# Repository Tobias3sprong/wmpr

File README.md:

# Weller WMPR
Weller WMPR Solder controller

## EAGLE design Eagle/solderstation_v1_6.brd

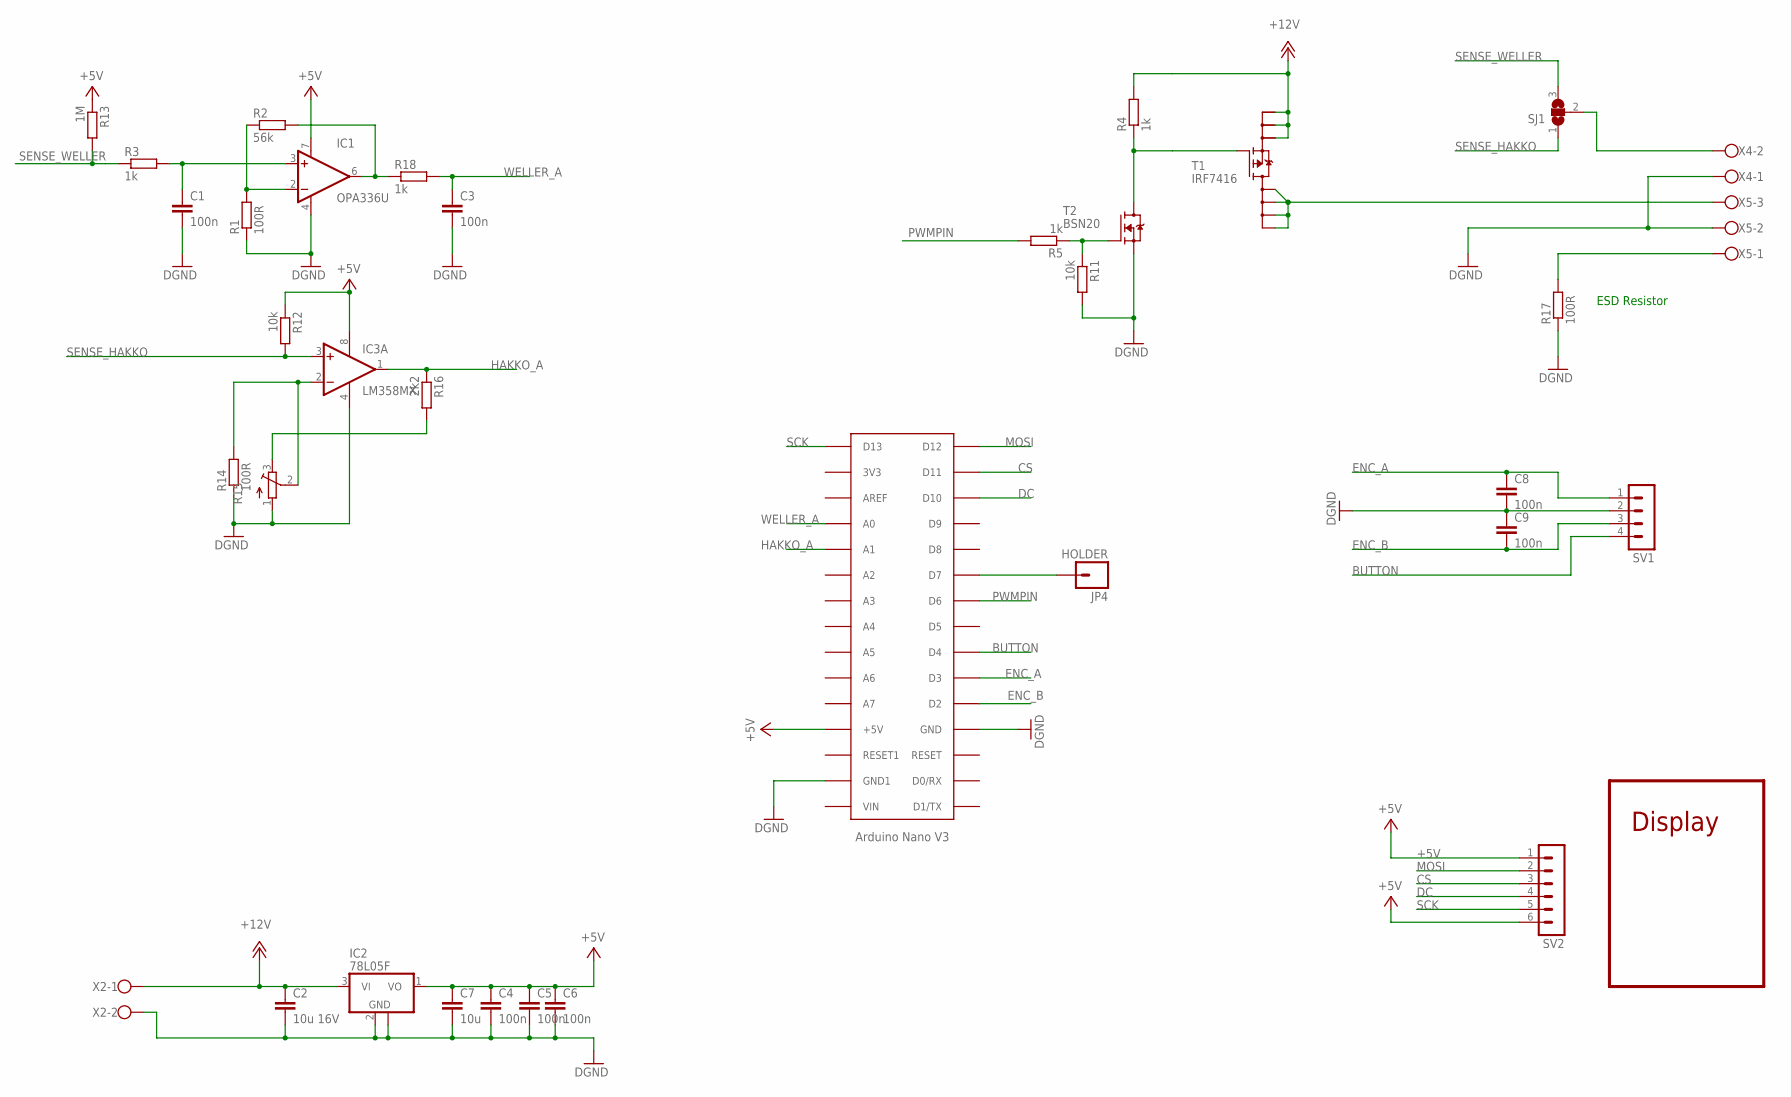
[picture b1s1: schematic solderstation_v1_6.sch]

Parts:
C1, C3, C4, C5, C6, C8, C9: 100n; C1206
C2: 10u 16V; C1210K
C7: 10u; C1210K
IC1: OPA336U; SO08
IC2: 78L05F; SOT89
IC3: LM358MX; SO08
JP4: HOLDER; 1X01
R1, R14, R17: 100R; R0603
R2: 56k; R0603
R3, R4, R5, R18: 1k; R0603
R11, R12: 10k; R0603
R13: 1M; R0603
R15: TRIM_EU-SM-42/43X; SM-42/43X
R16: 2k2; R0603
SJ1: SJ2W; SJ_2
SV1: MA04-1
SV2: MA06-1
T1: IRF7416; SO8
T2: BSN20; SOT23
U$6: ARDUINONANO; PDIP-32
X2, X4: W237-102
X5: W237-103

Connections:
+5V: C4.1, C5.1, C6.1, C7.1, IC1.7 (V+), IC2.1 (VO), IC3.8 (V+), R12.1, R13.1, SV2.1, SV2.6, U$6.+5V
+12V: C2.1, IC2.3 (VI), R4.2, T1.1 (S0), T1.2 (S1), T1.3 (S2), X2.1
BUTTON: SV1.4, U$6.D4
CS: SV2.3, U$6.D11
DC: SV2.4, U$6.D10
DGND: C1.2, C2.2, C3.2, C4.2, C5.2, C6.2, C7.2, C8.2, C9.1, IC1.4 (V-), IC2.2 (GND), IC2.2@1 (GND), IC3.4 (V-), R1.1, R11.2, R14.1, R15.1 (A), R17.1, SV1.2, T2.2 (S), U$6.GND, U$6.GND1, X2.2, X4.1, X5.2
ENC_A: C8.1, SV1.1, U$6.D3
ENC_B: C9.2, SV1.3, U$6.D2
HAKKO_A: IC3.1 (OUT), R16.1, U$6.A6 (A1)
HEATER: T1.5 (D0), T1.6 (D1), T1.7 (D2), T1.8 (D3), X5.3
MOSI: SV2.2, U$6.D12
unnamed: IC1.2 (-IN), R1.2, R2.1
unnamed: IC1.6 (OUT), R2.2, R18.1
unnamed: R5.1, R11.1, T2.1 (G)
unnamed: C1.1, IC1.3 (+IN), R3.2
unnamed: R4.1, T1.4 (G), T2.3 (D)
unnamed: SJ1.2, X4.2
unnamed: R15.3 (E), R16.2
unnamed: IC3.2 (-IN), R14.2, R15.2 (S)
unnamed: JP4.1, U$6.D7
unnamed: R17.2, X5.1
PWMPIN: R5.2, U$6.D6
SCK: SV2.5, U$6.D13
SENSE_HAKKO: IC3.3 (+IN), R12.2, SJ1.1
SENSE_WELLER: R3.1, R13.2, SJ1.3
WELLER_A: C3.1, R18.2, U$6.A7 (A0)

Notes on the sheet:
Display
ESD Resistor

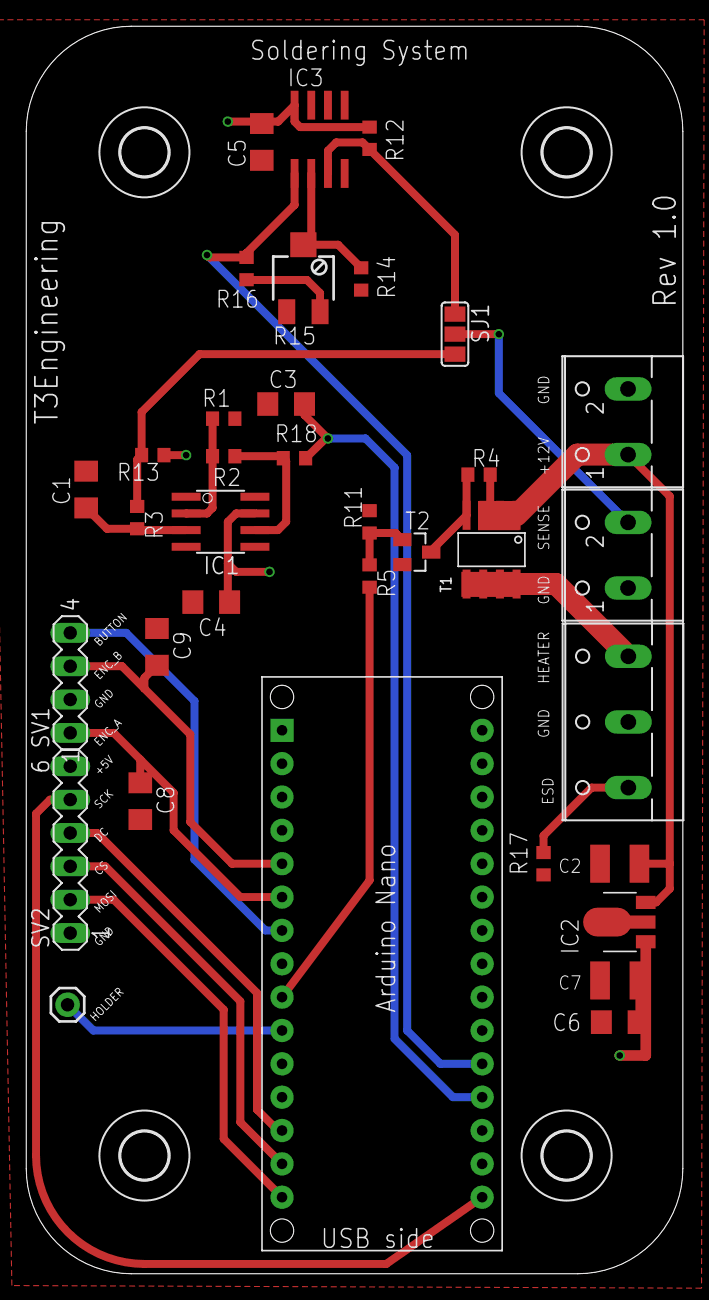
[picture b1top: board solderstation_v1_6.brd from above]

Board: 2 copper layers, 50.0 x 95.0 mm, 39 parts (0 on the bottom side), 26 nets.

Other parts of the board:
U$1, U$2, U$4, U$5: 3,6

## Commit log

2017-01-10 PCB and Arduino code added
2017-01-10 deleted Eagle backup files
2017-01-10 Added standby function

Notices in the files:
parts and their libraries:
SparkFun: Licensing: CC v3.0 Share-Alike You are welcome to use this library for commercial purposes.
